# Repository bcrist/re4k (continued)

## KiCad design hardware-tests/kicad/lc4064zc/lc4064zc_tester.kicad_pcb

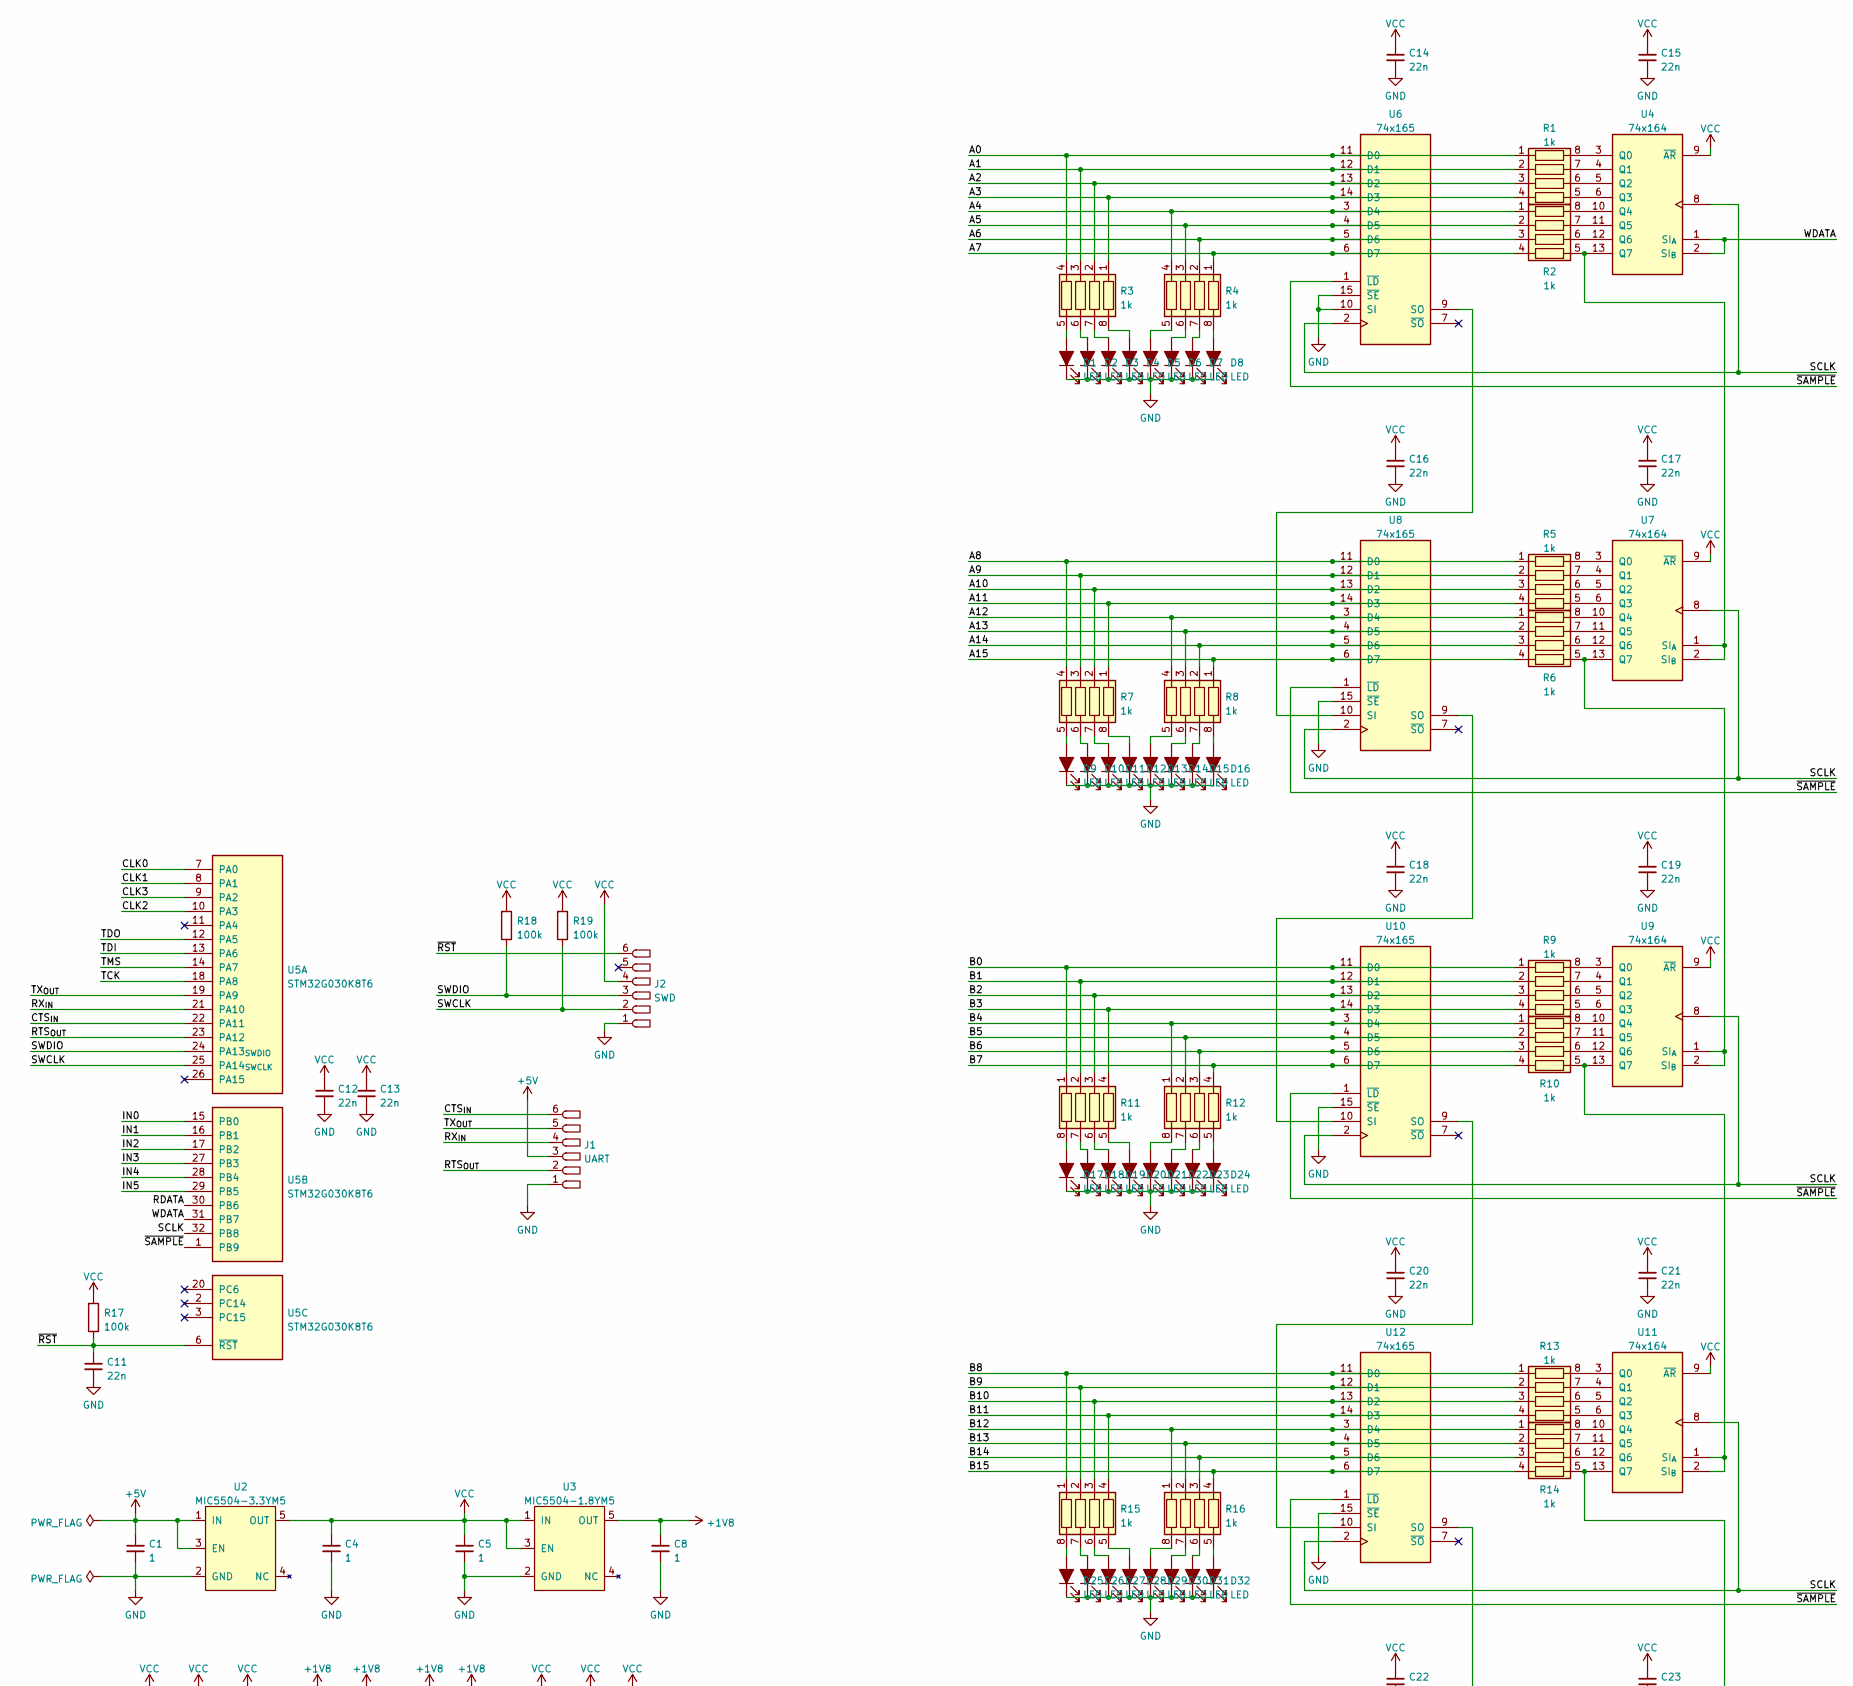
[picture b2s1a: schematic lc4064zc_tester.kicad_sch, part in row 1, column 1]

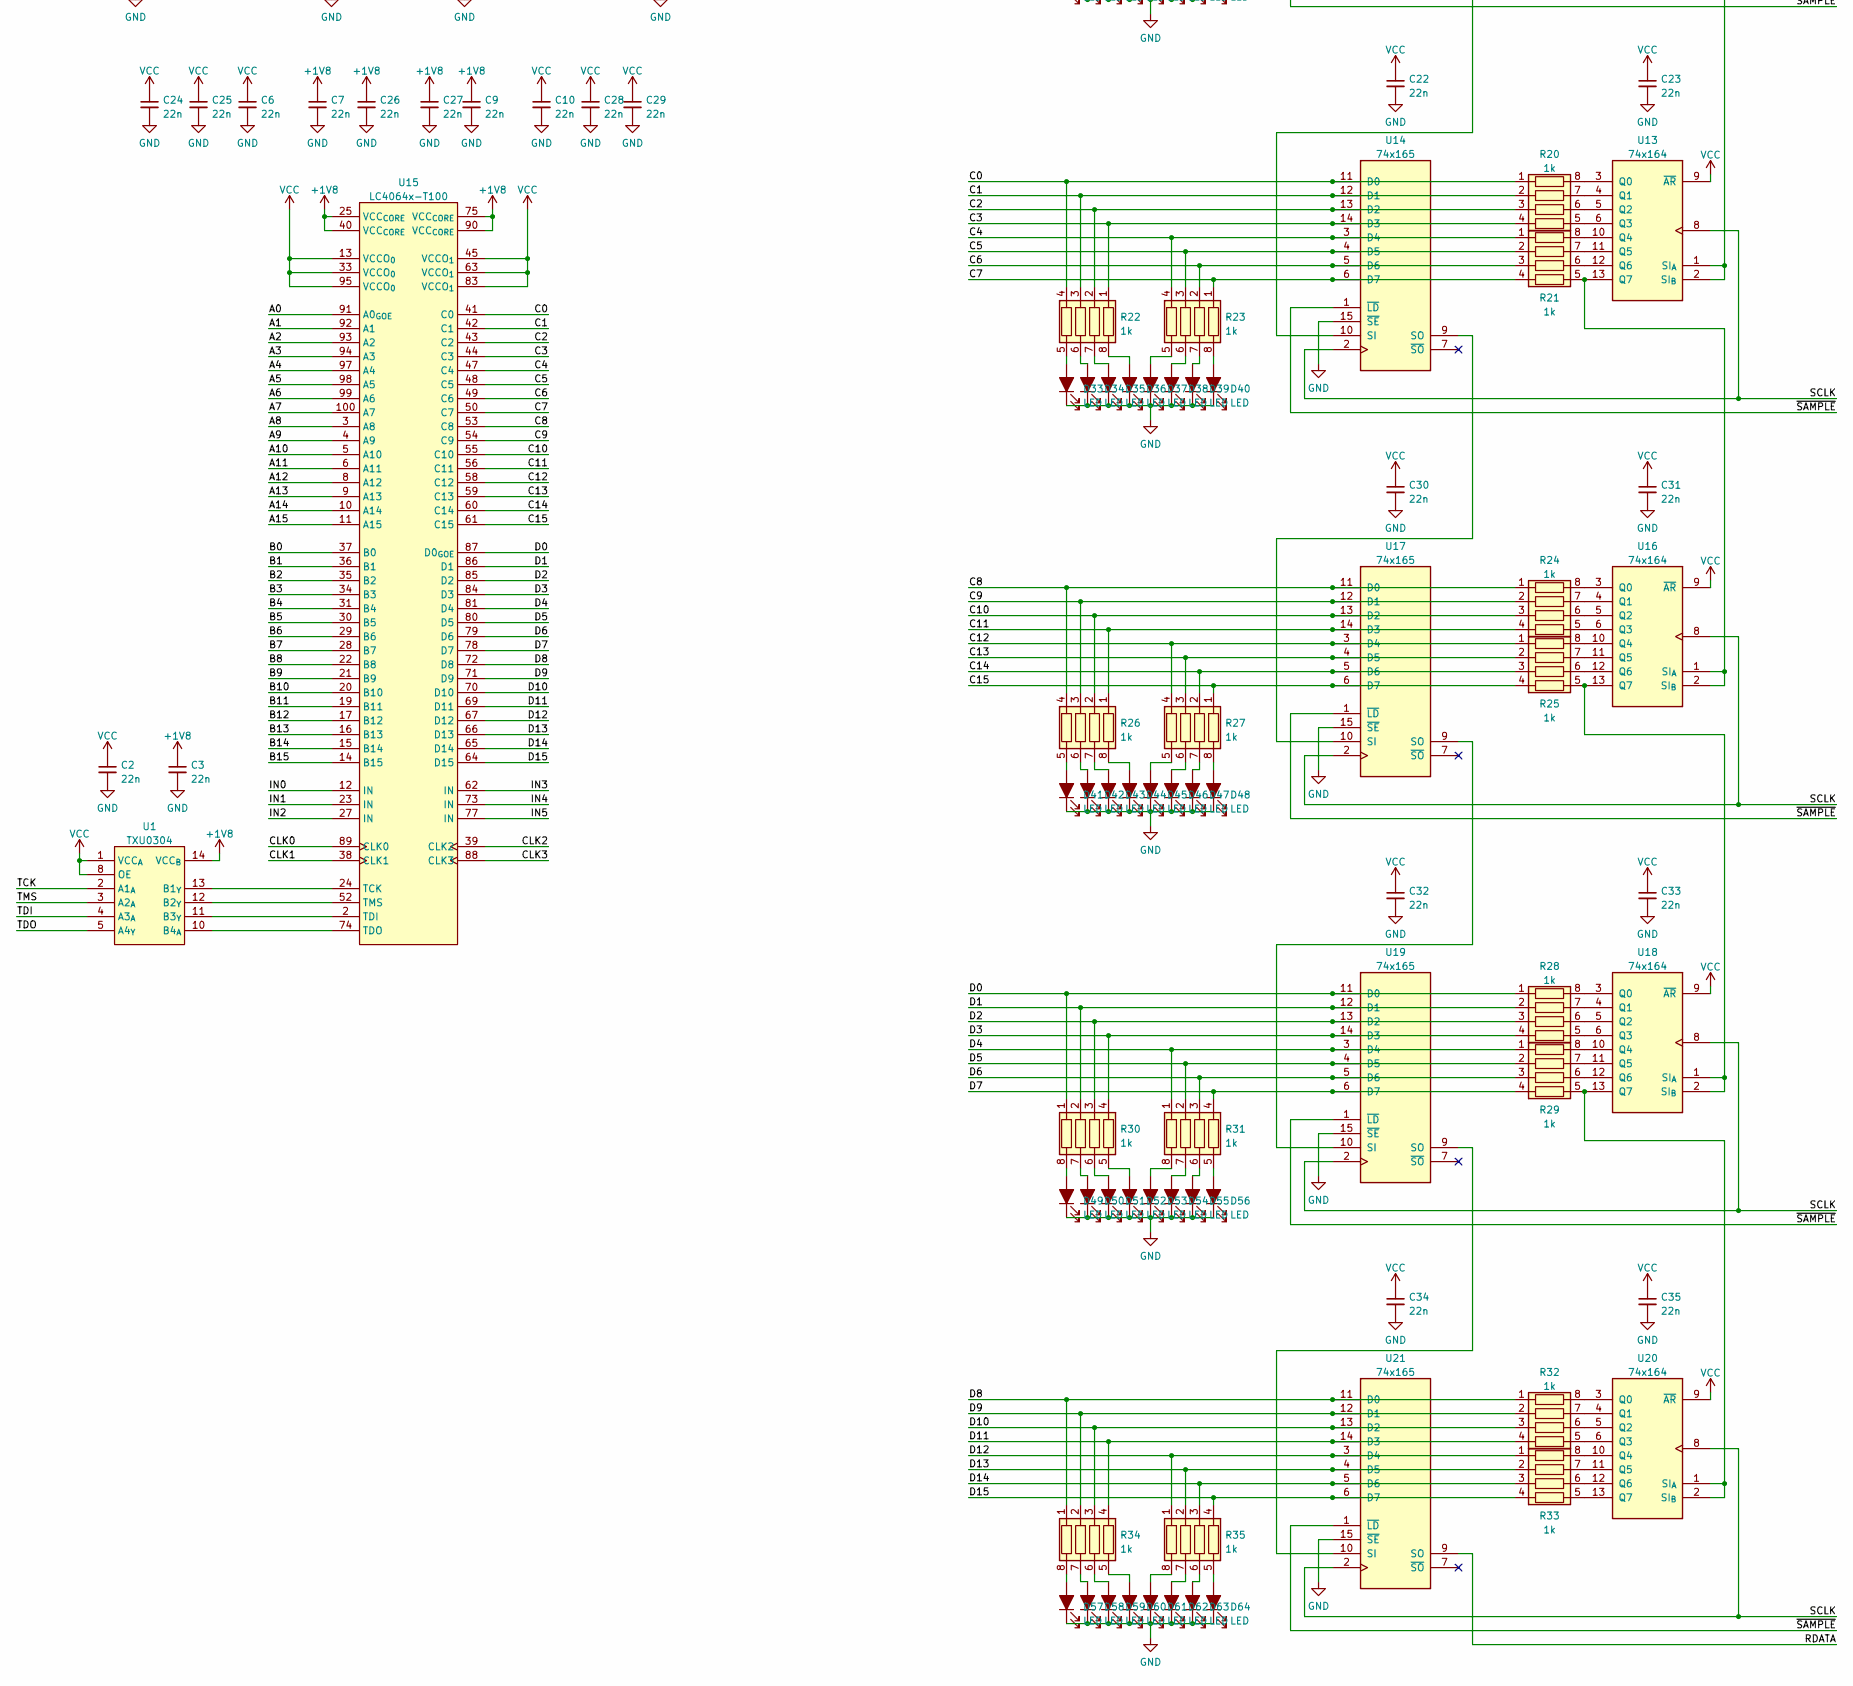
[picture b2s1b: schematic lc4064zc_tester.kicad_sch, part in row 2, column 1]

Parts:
C1, C4, C5, C8: 1; C_0603
C2, C3, C6, C7, C9, C10, C11, C12, C13, C14, C15, C16, C17, C18, C19, C20, C21, C22, C23, C24, C25, C26, C27, C28, C29, C30, C31, C32, C33, C34, C35: 22n; C_0603
D1, D2, D3, D4, D5, D6, D7, D8, D9, D10, D11, D12, D13, D14, D15, D16, D17, D18, D19, D20, D21, D22, D23, D24, D25, D26, D27, D28, D29, D30, D31, D32, D33, D34, D35, D36, D37, D38, D39, D40, D41, D42, D43, D44, D45, D46, D47, D48, D49, D50, D51, D52, D53, D54, D55, D56, D57, D58, D59, D60, D61, D62, D63, D64: LED; LED_0603
J1: UART; header_1x6
J2: SWD; header_1x6
R1, R2, R3, R4, R5, R6, R7, R8, R9, R10, R11, R12, R13, R14, R15, R16, R20, R21, R22, R23, R24, R25, R26, R27, R28, R29, R30, R31, R32, R33, R34, R35: 1k; R_0408-8
R17, R18, R19: 100k; R_0603
U1: TXU0304; U_TSSOP-14_4.4x5_P0.65
U2: MIC5504-3.3YM5; U_SOT23-5
U3: MIC5504-1.8YM5; U_SOT23-5
U4, U7, U9, U11, U13, U16, U18, U20: 74x164; U_TSSOP-14_4.4x5_P0.65
U5: STM32G030K8T6; U_QFP-32_7x7_P0.8
U6, U8, U10, U12, U14, U17, U19, U21: 74x165; U_TSSOP-16_4.4x5_P0.65
U15: LC4064x-T100; U_QFP-100_14x14_P0.5

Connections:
+1V8: C3.1, C7.1, C8.1, C9.1, C26.1, C27.1, U1.14 (VCC_{B}), U3.5 (OUT), U15.25 (VCC_{CORE}), U15.40 (VCC_{CORE}), U15.75 (VCC_{CORE}), U15.90 (VCC_{CORE})
+5V: C1.1, J1.3, U2.1 (IN), U2.3 (EN)
/A0: R1.1, R3.4, U6.11 (D0), U15.91 (A0_{GOE})
/A1: R1.2, R3.3, U6.12 (D1), U15.92 (A1)
/A2: R1.3, R3.2, U6.13 (D2), U15.93 (A2)
/A3: R1.4, R3.1, U6.14 (D3), U15.94 (A3)
/A4: R2.1, R4.4, U6.3 (D4), U15.97 (A4)
/A5: R2.2, R4.3, U6.4 (D5), U15.98 (A5)
/A6: R2.3, R4.2, U6.5 (D6), U15.99 (A6)
/A7: R2.4, R4.1, U6.6 (D7), U15.100 (A7)
/A8: R5.1, R7.4, U8.11 (D0), U15.3 (A8)
/A9: R5.2, R7.3, U8.12 (D1), U15.4 (A9)
/A10: R5.3, R7.2, U8.13 (D2), U15.5 (A10)
/A11: R5.4, R7.1, U8.14 (D3), U15.6 (A11)
/A12: R6.1, R8.4, U8.3 (D4), U15.8 (A12)
/A13: R6.2, R8.3, U8.4 (D5), U15.9 (A13)
/A14: R6.3, R8.2, U8.5 (D6), U15.10 (A14)
/A15: R6.4, R8.1, U8.6 (D7), U15.11 (A15)
/B0: R9.1, R11.1, U10.11 (D0), U15.37 (B0)
/B1: R9.2, R11.2, U10.12 (D1), U15.36 (B1)
/B2: R9.3, R11.3, U10.13 (D2), U15.35 (B2)
/B3: R9.4, R11.4, U10.14 (D3), U15.34 (B3)
/B4: R10.1, R12.1, U10.3 (D4), U15.31 (B4)
/B5: R10.2, R12.2, U10.4 (D5), U15.30 (B5)
/B6: R10.3, R12.3, U10.5 (D6), U15.29 (B6)
/B7: R10.4, R12.4, U10.6 (D7), U15.28 (B7)
/B8: R13.1, R15.1, U12.11 (D0), U15.22 (B8)
/B9: R13.2, R15.2, U12.12 (D1), U15.21 (B9)
/B10: R13.3, R15.3, U12.13 (D2), U15.20 (B10)
/B11: R13.4, R15.4, U12.14 (D3), U15.19 (B11)
/B12: R14.1, R16.1, U12.3 (D4), U15.17 (B12)
/B13: R14.2, R16.2, U12.4 (D5), U15.16 (B13)
/B14: R14.3, R16.3, U12.5 (D6), U15.15 (B14)
/B15: R14.4, R16.4, U12.6 (D7), U15.14 (B15)
/C0: R20.1, R22.4, U14.11 (D0), U15.41 (C0)
/C1: R20.2, R22.3, U14.12 (D1), U15.42 (C1)
/C2: R20.3, R22.2, U14.13 (D2), U15.43 (C2)
/C3: R20.4, R22.1, U14.14 (D3), U15.44 (C3)
/C4: R21.1, R23.4, U14.3 (D4), U15.47 (C4)
/C5: R21.2, R23.3, U14.4 (D5), U15.48 (C5)
/C6: R21.3, R23.2, U14.5 (D6), U15.49 (C6)
/C7: R21.4, R23.1, U14.6 (D7), U15.50 (C7)
/C8: R24.1, R26.4, U15.53 (C8), U17.11 (D0)
/C9: R24.2, R26.3, U15.54 (C9), U17.12 (D1)
/C10: R24.3, R26.2, U15.55 (C10), U17.13 (D2)
/C11: R24.4, R26.1, U15.56 (C11), U17.14 (D3)
/C12: R25.1, R27.4, U15.58 (C12), U17.3 (D4)
/C13: R25.2, R27.3, U15.59 (C13), U17.4 (D5)
/C14: R25.3, R27.2, U15.60 (C14), U17.5 (D6)
/C15: R25.4, R27.1, U15.61 (C15), U17.6 (D7)
/CLK0: U5.7 (PA0), U15.89 (CLK0)
/CLK1: U5.8 (PA1), U15.38 (CLK1)
/CLK2: U5.10 (PA3), U15.39 (CLK2)
/CLK3: U5.9 (PA2), U15.88 (CLK3)
/CTS_{IN}: J1.6, U5.22 (PA11)
/D0: R28.1, R30.1, U15.87 (D0_{GOE}), U19.11 (D0)
/D1: R28.2, R30.2, U15.86 (D1), U19.12 (D1)
/D2: R28.3, R30.3, U15.85 (D2), U19.13 (D2)
/D3: R28.4, R30.4, U15.84 (D3), U19.14 (D3)
/D4: R29.1, R31.1, U15.81 (D4), U19.3 (D4)
/D5: R29.2, R31.2, U15.80 (D5), U19.4 (D5)
/D6: R29.3, R31.3, U15.79 (D6), U19.5 (D6)
/D7: R29.4, R31.4, U15.78 (D7), U19.6 (D7)
/D8: R32.1, R34.1, U15.72 (D8), U21.11 (D0)
/D9: R32.2, R34.2, U15.71 (D9), U21.12 (D1)
/D10: R32.3, R34.3, U15.70 (D10), U21.13 (D2)
/D11: R32.4, R34.4, U15.69 (D11), U21.14 (D3)
/D12: R33.1, R35.1, U15.67 (D12), U21.3 (D4)
/D13: R33.2, R35.2, U15.66 (D13), U21.4 (D5)
/D14: R33.3, R35.3, U15.65 (D14), U21.5 (D6)
/D15: R33.4, R35.4, U15.64 (D15), U21.6 (D7)
/IN0: U5.15 (PB0), U15.12 (IN)
/IN1: U5.16 (PB1), U15.23 (IN)
/IN2: U5.17 (PB2), U15.27 (IN)
/IN3: U5.27 (PB3), U15.62 (IN)
/IN4: U5.28 (PB4), U15.73 (IN)
/IN5: U5.29 (PB5), U15.77 (IN)
/RDATA: U5.30 (PB6), U21.9 (SO)
/RTS_{OUT}: J1.2, U5.23 (PA12)
/RX_{IN}: J1.4, U5.21 (PA10)
/SCLK: U4.8, U5.32 (PB8), U6.2, U7.8, U8.2, U9.8, U10.2, U11.8, U12.2, U13.8, U14.2, U16.8, U17.2, U18.8, U19.2, U20.8, U21.2
/SWCLK: J2.2, R19.2, U5.25 (PA14_{SWCLK})
/SWDIO: J2.3, R18.2, U5.24 (PA13_{SWDIO})
/TCK: U1.2 (A1_{A}), U5.18 (PA8)
/TDI: U1.4 (A3_{A}), U5.13 (PA6)
/TDO: U1.5 (A4_{Y}), U5.12 (PA5)
/TMS: U1.3 (A2_{A}), U5.14 (PA7)
/TX_{OUT}: J1.5, U5.19 (PA9)
/WDATA: U4.1 (SI_{A}), U4.2 (SI_{B}), U5.31 (PB7)
/~RST: C11.1, J2.6, R17.2, U5.6 (~RST)
/~SAMPLE: U5.1 (PB9), U6.1 (~LD), U8.1 (~LD), U10.1 (~LD), U12.1 (~LD), U14.1 (~LD), U17.1 (~LD), U19.1 (~LD), U21.1 (~LD)
GND: C1.2, C2.2, C3.2, C4.2, C5.2, C6.2, C7.2, C8.2, C9.2, C10.2, C11.2, C12.2, C13.2, C14.2, C15.2, C16.2, C17.2, C18.2, C19.2, C20.2, C21.2, C22.2, C23.2, C24.2, C25.2, C26.2, C27.2, C28.2, C29.2, C30.2, C31.2, C32.2, C33.2, C34.2, C35.2, D1.1 (K), D2.1 (K), D3.1 (K), D4.1 (K), D5.1 (K), D6.1 (K), D7.1 (K), D8.1 (K), D9.1 (K), D10.1 (K), D11.1 (K), D12.1 (K), D13.1 (K), D14.1 (K), D15.1 (K), D16.1 (K), D17.1 (K), D18.1 (K), D19.1 (K), D20.1 (K), D21.1 (K), D22.1 (K), D23.1 (K), D24.1 (K), D25.1 (K), D26.1 (K), D27.1 (K), D28.1 (K), D29.1 (K), D30.1 (K), D31.1 (K), D32.1 (K), D33.1 (K), D34.1 (K), D35.1 (K), D36.1 (K), D37.1 (K), D38.1 (K), D39.1 (K), D40.1 (K), D41.1 (K), D42.1 (K), D43.1 (K), D44.1 (K), D45.1 (K), D46.1 (K), D47.1 (K), D48.1 (K), D49.1 (K), D50.1 (K), D51.1 (K), D52.1 (K), D53.1 (K), D54.1 (K), D55.1 (K), D56.1 (K), D57.1 (K), D58.1 (K), D59.1 (K), D60.1 (K), D61.1 (K), D62.1 (K), D63.1 (K), D64.1 (K), J1.1, J2.1, U1.7 (GND), U2.2 (GND), U3.2 (GND), U4.7 (GND), U5.5 (GND), U6.8 (GND), U6.10 (SI), U6.15 (~SE), U7.7 (GND), U8.8 (GND), U8.15 (~SE), U9.7 (GND), U10.8 (GND), U10.15 (~SE), U11.7 (GND), U12.8 (GND), U12.15 (~SE), U13.7 (GND), U14.8 (GND), U14.15 (~SE), U15.1 (GND), U15.7 (GND), U15.18 (GND), U15.26 (GND), U15.32 (GND), U15.46 (GND), U15.51 (GND), U15.57 (GND), U15.68 (GND), U15.76 (GND), U15.82 (GND), U15.96 (GND), U16.7 (GND), U17.8 (GND), U17.15 (~SE), U18.7 (GND), U19.8 (GND), U19.15 (~SE), U20.7 (GND), U21.8 (GND), U21.15 (~SE)
unnamed: D1.2 (A), R3.5
unnamed: D2.2 (A), R3.6
unnamed: D3.2 (A), R3.7
unnamed: D4.2 (A), R3.8
unnamed: D5.2 (A), R4.5
unnamed: D6.2 (A), R4.6
unnamed: D7.2 (A), R4.7
unnamed: D8.2 (A), R4.8
unnamed: D9.2 (A), R7.5
unnamed: D10.2 (A), R7.6
unnamed: D11.2 (A), R7.7
unnamed: D12.2 (A), R7.8
unnamed: D13.2 (A), R8.5
unnamed: D14.2 (A), R8.6
unnamed: D15.2 (A), R8.7
unnamed: D16.2 (A), R8.8
unnamed: D17.2 (A), R11.8
unnamed: D18.2 (A), R11.7
unnamed: D19.2 (A), R11.6
unnamed: D20.2 (A), R11.5
unnamed: D21.2 (A), R12.8
unnamed: D22.2 (A), R12.7
unnamed: D23.2 (A), R12.6
unnamed: D24.2 (A), R12.5
unnamed: D25.2 (A), R15.8
unnamed: D26.2 (A), R15.7
unnamed: D27.2 (A), R15.6
unnamed: D28.2 (A), R15.5
unnamed: D29.2 (A), R16.8
unnamed: D30.2 (A), R16.7
unnamed: D31.2 (A), R16.6
unnamed: D32.2 (A), R16.5
unnamed: D33.2 (A), R22.5
unnamed: D34.2 (A), R22.6
unnamed: D35.2 (A), R22.7
unnamed: D36.2 (A), R22.8
unnamed: D37.2 (A), R23.5
unnamed: D38.2 (A), R23.6
unnamed: D39.2 (A), R23.7
unnamed: D40.2 (A), R23.8
unnamed: D41.2 (A), R26.5
unnamed: D42.2 (A), R26.6
unnamed: D43.2 (A), R26.7
unnamed: D44.2 (A), R26.8
unnamed: D45.2 (A), R27.5
unnamed: D46.2 (A), R27.6
unnamed: D47.2 (A), R27.7
unnamed: D48.2 (A), R27.8
unnamed: D49.2 (A), R30.8
unnamed: D50.2 (A), R30.7
unnamed: D51.2 (A), R30.6
unnamed: D52.2 (A), R30.5
unnamed: D53.2 (A), R31.8
unnamed: D54.2 (A), R31.7
unnamed: D55.2 (A), R31.6
unnamed: D56.2 (A), R31.5
unnamed: D57.2 (A), R34.8
unnamed: D58.2 (A), R34.7
unnamed: D59.2 (A), R34.6
unnamed: D60.2 (A), R34.5
unnamed: D61.2 (A), R35.8
unnamed: D62.2 (A), R35.7
unnamed: D63.2 (A), R35.6
unnamed: D64.2 (A), R35.5
unnamed: R1.5, U4.6 (Q3)
unnamed: R1.6, U4.5 (Q2)
unnamed: R1.7, U4.4 (Q1)
unnamed: R1.8, U4.3 (Q0)
unnamed: R2.5, U4.13 (Q7), U7.1 (SI_{A}), U7.2 (SI_{B})
unnamed: R2.6, U4.12 (Q6)
unnamed: R2.7, U4.11 (Q5)
unnamed: R2.8, U4.10 (Q4)
unnamed: R5.5, U7.6 (Q3)
unnamed: R5.6, U7.5 (Q2)
unnamed: R5.7, U7.4 (Q1)
unnamed: R5.8, U7.3 (Q0)
unnamed: R6.5, U7.13 (Q7), U9.1 (SI_{A}), U9.2 (SI_{B})
unnamed: R6.6, U7.12 (Q6)
unnamed: R6.7, U7.11 (Q5)
unnamed: R6.8, U7.10 (Q4)
unnamed: R9.5, U9.6 (Q3)
unnamed: R9.6, U9.5 (Q2)
unnamed: R9.7, U9.4 (Q1)
unnamed: R9.8, U9.3 (Q0)
unnamed: R10.5, U9.13 (Q7), U11.1 (SI_{A}), U11.2 (SI_{B})
unnamed: R10.6, U9.12 (Q6)
unnamed: R10.7, U9.11 (Q5)
unnamed: R10.8, U9.10 (Q4)
unnamed: R13.5, U11.6 (Q3)
unnamed: R13.6, U11.5 (Q2)
unnamed: R13.7, U11.4 (Q1)
unnamed: R13.8, U11.3 (Q0)
unnamed: R14.5, U11.13 (Q7), U13.1 (SI_{A}), U13.2 (SI_{B})
unnamed: R14.6, U11.12 (Q6)
unnamed: R14.7, U11.11 (Q5)
unnamed: R14.8, U11.10 (Q4)
unnamed: R20.5, U13.6 (Q3)
unnamed: R20.6, U13.5 (Q2)
unnamed: R20.7, U13.4 (Q1)
unnamed: R20.8, U13.3 (Q0)
unnamed: R21.5, U13.13 (Q7), U16.1 (SI_{A}), U16.2 (SI_{B})
unnamed: R21.6, U13.12 (Q6)
unnamed: R21.7, U13.11 (Q5)
unnamed: R21.8, U13.10 (Q4)
unnamed: R24.5, U16.6 (Q3)
unnamed: R24.6, U16.5 (Q2)
unnamed: R24.7, U16.4 (Q1)
unnamed: R24.8, U16.3 (Q0)
unnamed: R25.5, U16.13 (Q7), U18.1 (SI_{A}), U18.2 (SI_{B})
unnamed: R25.6, U16.12 (Q6)
unnamed: R25.7, U16.11 (Q5)
unnamed: R25.8, U16.10 (Q4)
unnamed: R28.5, U18.6 (Q3)
unnamed: R28.6, U18.5 (Q2)
unnamed: R28.7, U18.4 (Q1)
unnamed: R28.8, U18.3 (Q0)
unnamed: R29.5, U18.13 (Q7), U20.1 (SI_{A}), U20.2 (SI_{B})
unnamed: R29.6, U18.12 (Q6)
unnamed: R29.7, U18.11 (Q5)
unnamed: R29.8, U18.10 (Q4)
unnamed: R32.5, U20.6 (Q3)
unnamed: R32.6, U20.5 (Q2)
unnamed: R32.7, U20.4 (Q1)
unnamed: R32.8, U20.3 (Q0)
unnamed: R33.5, U20.13 (Q7)
unnamed: R33.6, U20.12 (Q6)
unnamed: R33.7, U20.11 (Q5)
unnamed: R33.8, U20.10 (Q4)
unnamed: U1.10 (B4_{A}), U15.74 (TDO)
unnamed: U1.11 (B3_{Y}), U15.2 (TDI)
unnamed: U1.12 (B2_{Y}), U15.52 (TMS)
unnamed: U1.13 (B1_{Y}), U15.24 (TCK)
unnamed: U6.9 (SO), U8.10 (SI)
unnamed: U10.9 (SO), U12.10 (SI)
unnamed: U8.9 (SO), U10.10 (SI)
unnamed: U12.9 (SO), U14.10 (SI)
unnamed: U14.9 (SO), U17.10 (SI)
unnamed: U17.9 (SO), U19.10 (SI)
unnamed: U19.9 (SO), U21.10 (SI)
VCC: C2.1, C4.1, C5.1, C6.1, C10.1, C12.1, C13.1, C14.1, C15.1, C16.1, C17.1, C18.1, C19.1, C20.1, C21.1, C22.1, C23.1, C24.1, C25.1, C28.1, C29.1, C30.1, C31.1, C32.1, C33.1, C34.1, C35.1, J2.4, R17.1, R18.1, R19.1, U1.1 (VCC_{A}), U1.8 (OE), U2.5 (OUT), U3.1 (IN), U3.3 (EN), U4.9 (~AR), U4.14 (VCC), U5.4 (VCC), U6.16 (VCC), U7.9 (~AR), U7.14 (VCC), U8.16 (VCC), U9.9 (~AR), U9.14 (VCC), U10.16 (VCC), U11.9 (~AR), U11.14 (VCC), U12.16 (VCC), U13.9 (~AR), U13.14 (VCC), U14.16 (VCC), U15.13 (VCCO_{0}), U15.33 (VCCO_{0}), U15.45 (VCCO_{1}), U15.63 (VCCO_{1}), U15.83 (VCCO_{1}), U15.95 (VCCO_{0}), U16.9 (~AR), U16.14 (VCC), U17.16 (VCC), U18.9 (~AR), U18.14 (VCC), U19.16 (VCC), U20.9 (~AR), U20.14 (VCC), U21.16 (VCC)

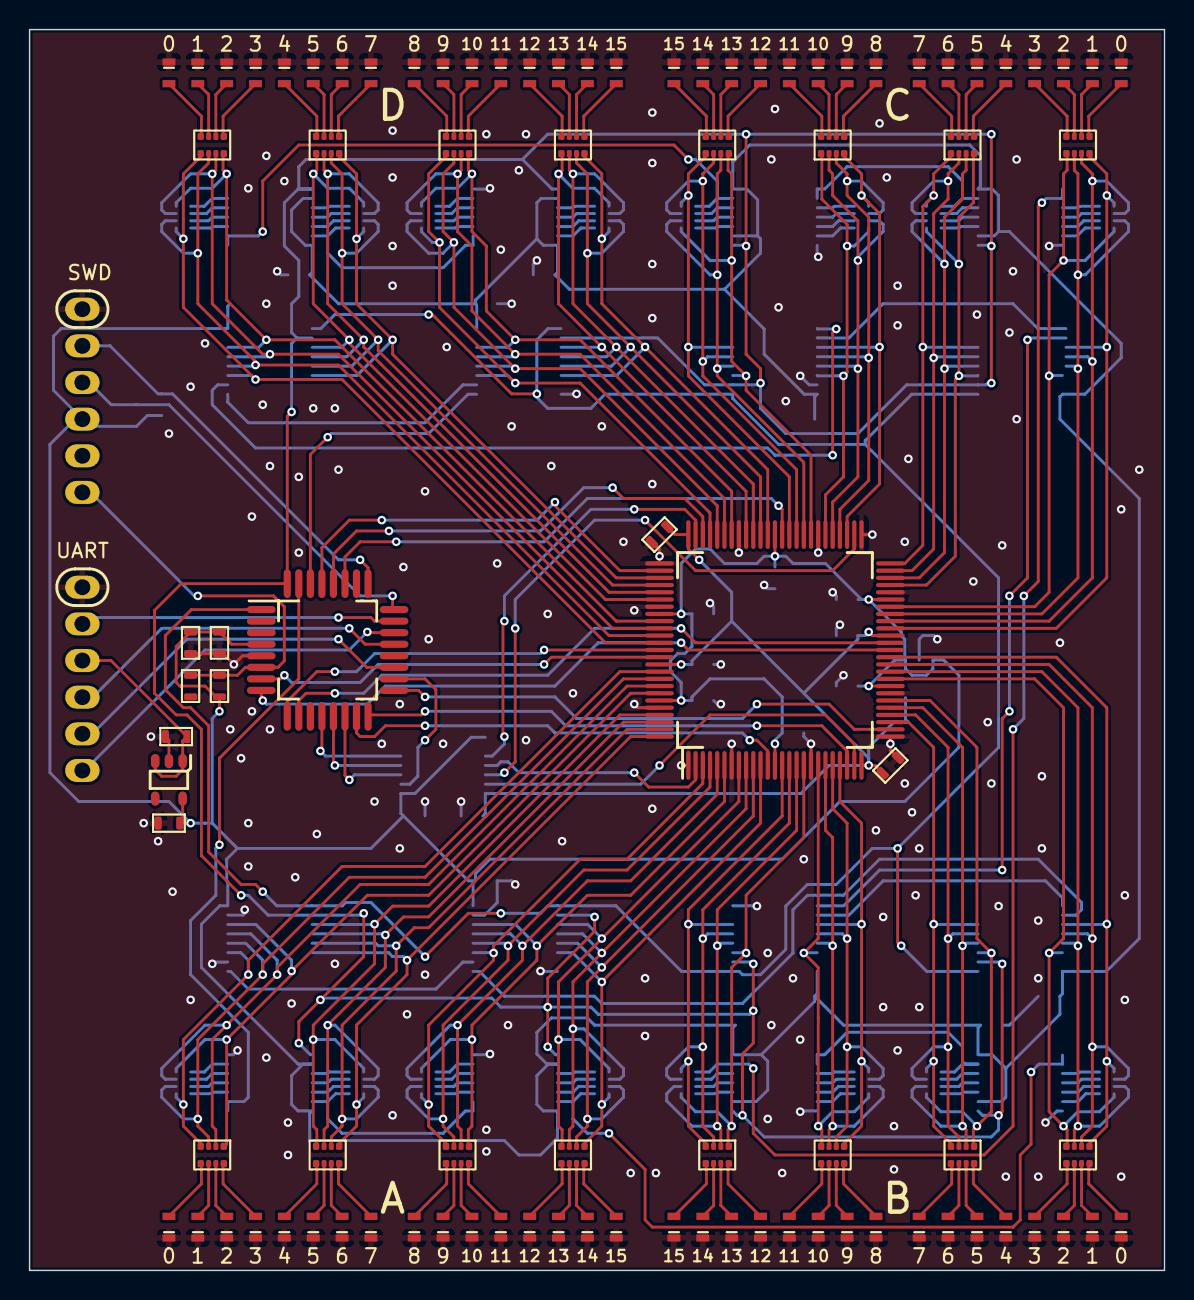
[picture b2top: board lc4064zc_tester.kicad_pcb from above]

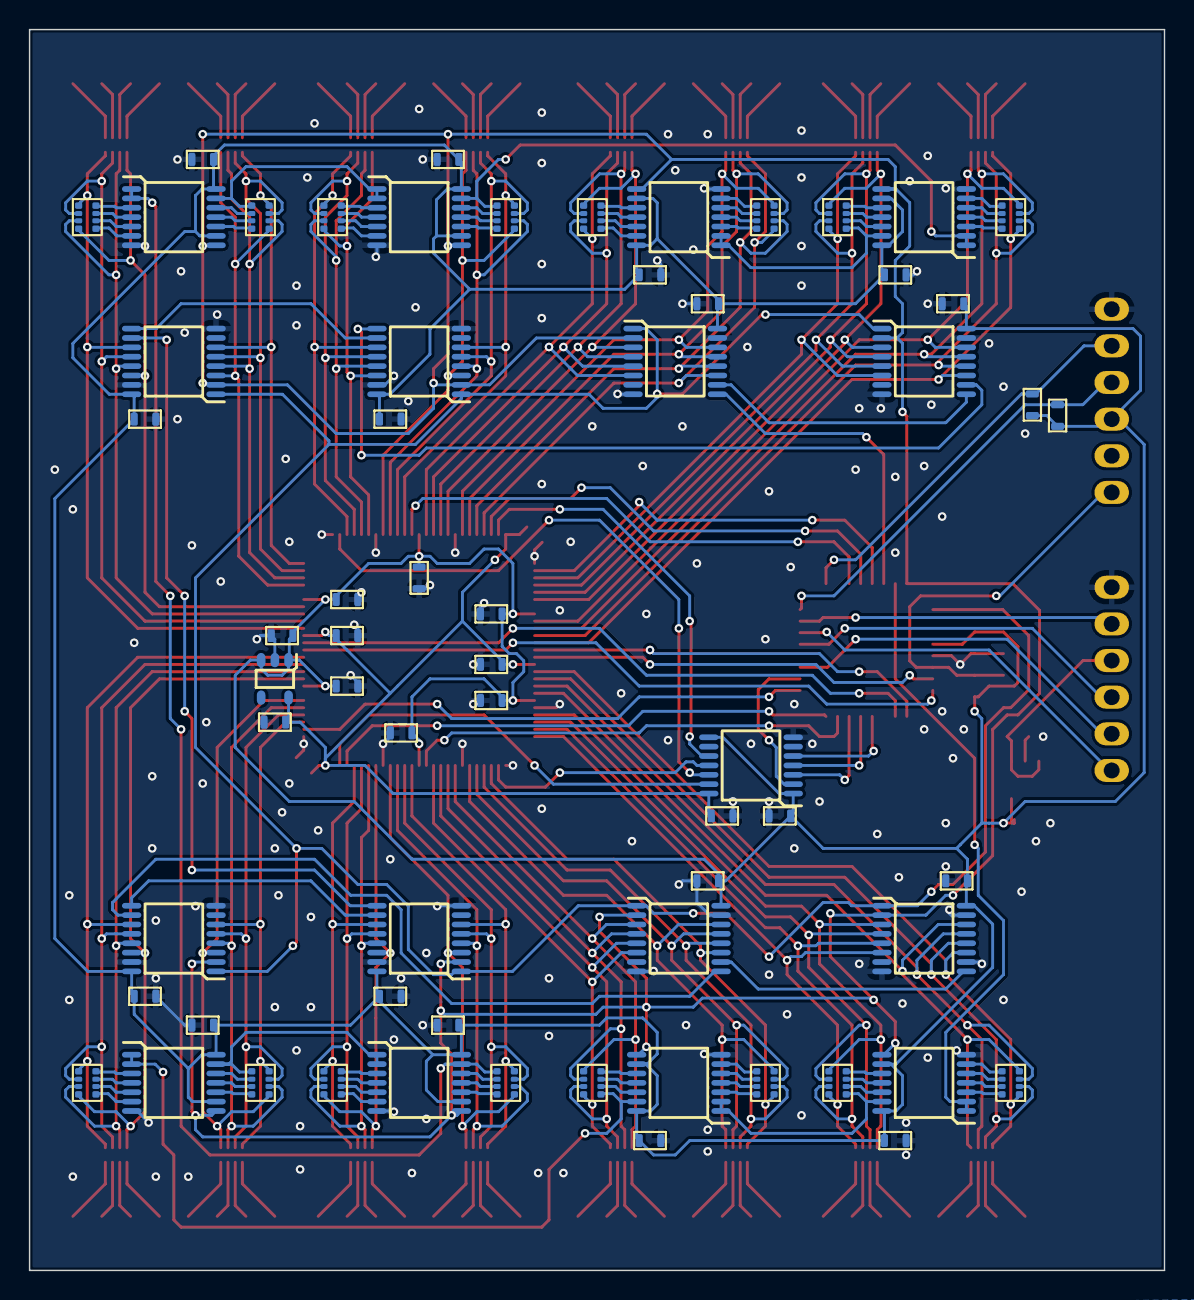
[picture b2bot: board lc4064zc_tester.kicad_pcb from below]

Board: 2 copper layers, 78.7 x 86.0 mm, 157 parts (64 on the bottom side), 232 nets.

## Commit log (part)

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2022-08-14 starting to get somewhere
2022-08-14 refactoring lua device data representation
2022-08-14 refactoring build_ninja.lua
2022-08-14 block clock muxes
2022-08-14 pgdf
2022-08-15 oe_mux and goe0/1 polarity
2022-08-17 orm fuses
2022-08-19 generate PLA files from lua rather than having ninja copy them. Add reset_init and ce_mux tests
2022-08-19 Don't overwrite lci files when regenerating build.ninja, unless their limp prologue needs to change
2022-08-21 pt0-pt3 fuses
2022-08-22 Add --exclude switch to jeddiff
2022-08-22 GLB input muxes (WIP)
2022-08-22 clean up ce_mux, add ff_type fuses
2022-08-24 various mc features
2022-08-24 cluster routing
2022-08-25 xor, inreg, osctimer, goe23 polarity
2022-08-30 JEDEC/SVF rework, starting work on automated reverse engineering of GLB inputs
2022-09-05 zerohold, slew rate using new toolchain strategy for more devices
2022-09-06 input threshold
2022-09-06 bus maintenance (buggy)
2022-09-06 drive type
2022-09-17 oe mux, orm
2022-09-17 powerup state
2022-09-17 add missing data
2022-09-17 ce_mux
2022-09-17 reg_type
2022-09-17 pt2_reset
2022-09-17 pt3_reset
2022-09-18 clk_mux
2022-09-20 cleanup, grp work
2022-09-22 grp for core devices, remove LC4256 support
2022-09-24 convert-grp
2022-09-24 pterms
2022-09-24 input registers
2022-09-24 sum/xor invert
2022-09-24 pt0_xor
2022-09-25 cluster_steering
2022-09-26 wide_steering
2022-10-18 gclk_polarity, output_routing_mode, hardware test work
2022-11-13 remove microzig submodule
2022-11-13 microbe, zig 0.10 updates
2022-11-19 hardware testing, LC4032ZE schematic
2022-11-19 remove unneccessary kicad .bak files
2022-11-19 change speed to 9600, work around LLVM issues formatting numbers > 128 bits
2022-11-19 add some test jed files
2022-11-19 documentation
2022-11-20 use Zig-SX submodule
2022-11-20 bugfixes, rebuild .sx files
2022-11-21 PT4 OE fuse
2022-11-21 fix gclk -> bclk
2022-11-22 shared PT polarity, GOE configuration
2022-11-22 power guard
2022-11-23 osctimer
2022-11-23 one () to rule them all
2022-11-23 cleanup, add glb/mc info to pin nodes
2022-11-23 refactoring naming conventions, add osctimer to LC4032ZE schematic
2022-11-23 invert naming
2022-11-23 bug documentation, add workaround for LC4064ZC_csBGA56 bug
2022-11-27 Refactor to use LC4k
2022-11-27 refactor reg_type => mc_func to match common.MacrocellFunction
2023-02-05 Adjustments for LC4k More fixes for LC4064ZC_csBGA56
2023-02-06 Update `pt4_oe.sx` to find fuses for all macrocells, not just outputs (buried macrocells can still contribute an OE via the ORM) Use fallback fuse data for E3 and F8 balls on LC4064ZC_csBGA56, which 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
2023-02-06 rename pull.sx to bus_maintenance.sx
2023-02-06 Update power_guard "enabled" state to "from_bie" Add ninja targets for cleaning a specific job type
2023-02-06 autogenerate the rest of the intermediary build.ninja files
2023-02-07 Fix compile errors in hardware testing firmware Improve accuracy of delays after JTAG commands Avoid sending ISC_DISABLE during reset (send it before and after programming instead)
2023-02-09 make LC4064ZC_csBGA56 threshold special cases a little less brittle
2023-02-09 Add notes on multiple GLBs driving same PT OE bus line
2023-02-09 remove obsolete test programs to generate hardware testing .jed files; replaced by lc4k examples dir
2023-02-10 Rename xor.sx -> input_bypass.sx (datasheet is wrong, it's not before XOR)
2023-02-11 Add documentation for s-expression files
2024-04-27 use zig build system instead of submodules, update for zig 0.12
2025-01-09 Updates for zig master, renaming in zig-lc4k
2025-01-09 pt4_output_enable fuses for all MCs, not just ones that have pads
2025-01-09 Use lc4k.Cluster_Routing in cluster_routing.zig
2025-01-09 Update wide_routing.zig to use lc4k.Wide_Routing names
2025-01-09 Fix root build.zig (noop)
2025-03-23 update for zig 0.14 package management changes
2025-07-29 Include bank info for Vcco associated ground pins
2025-09-15 zig 0.15.1
2025-10-25 LC4128ZC_BMC151 pinout
2025-11-29 BMC151 => BMC149
2026-02-22 zig 0.16
2026-02-28 add gh workflows
2026-03-25 Fix ArrayList issues
2026-04-03 Fix osctimer dynamic disable/reset fuse detection
2026-04-03 OSCTIMER dynamic disable/reset fuses
2026-04-03 OSCTIMER dynamic disable/reset fuses closes #1
2026-04-03 Add readme link to https://github.com/devsaurus/lc4k_core
2026-04-03 Remove TODOs from readme
2026-04-03 Bump version for OSCTIMER fixes
2026-04-12 zig 0.16 fixes
2026-05-04 remove ** usage
2026-05-24 BitSet.initEmpty() -> .empty
2026-05-26 update deps
